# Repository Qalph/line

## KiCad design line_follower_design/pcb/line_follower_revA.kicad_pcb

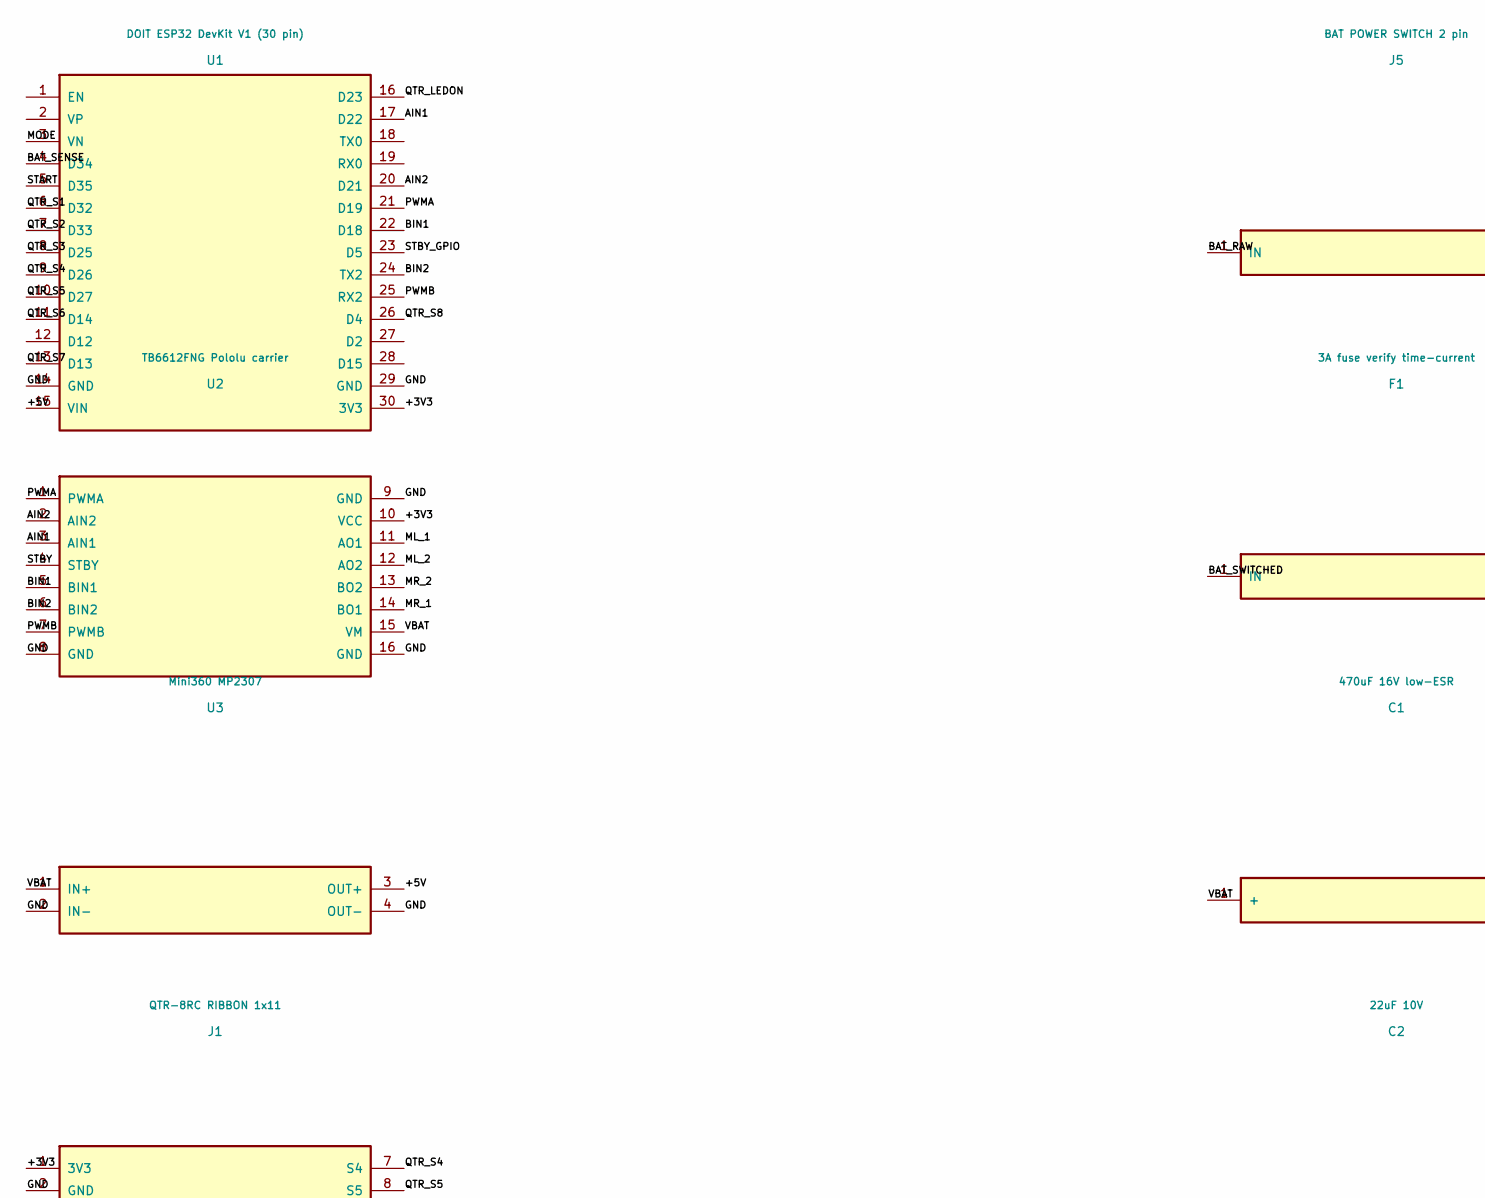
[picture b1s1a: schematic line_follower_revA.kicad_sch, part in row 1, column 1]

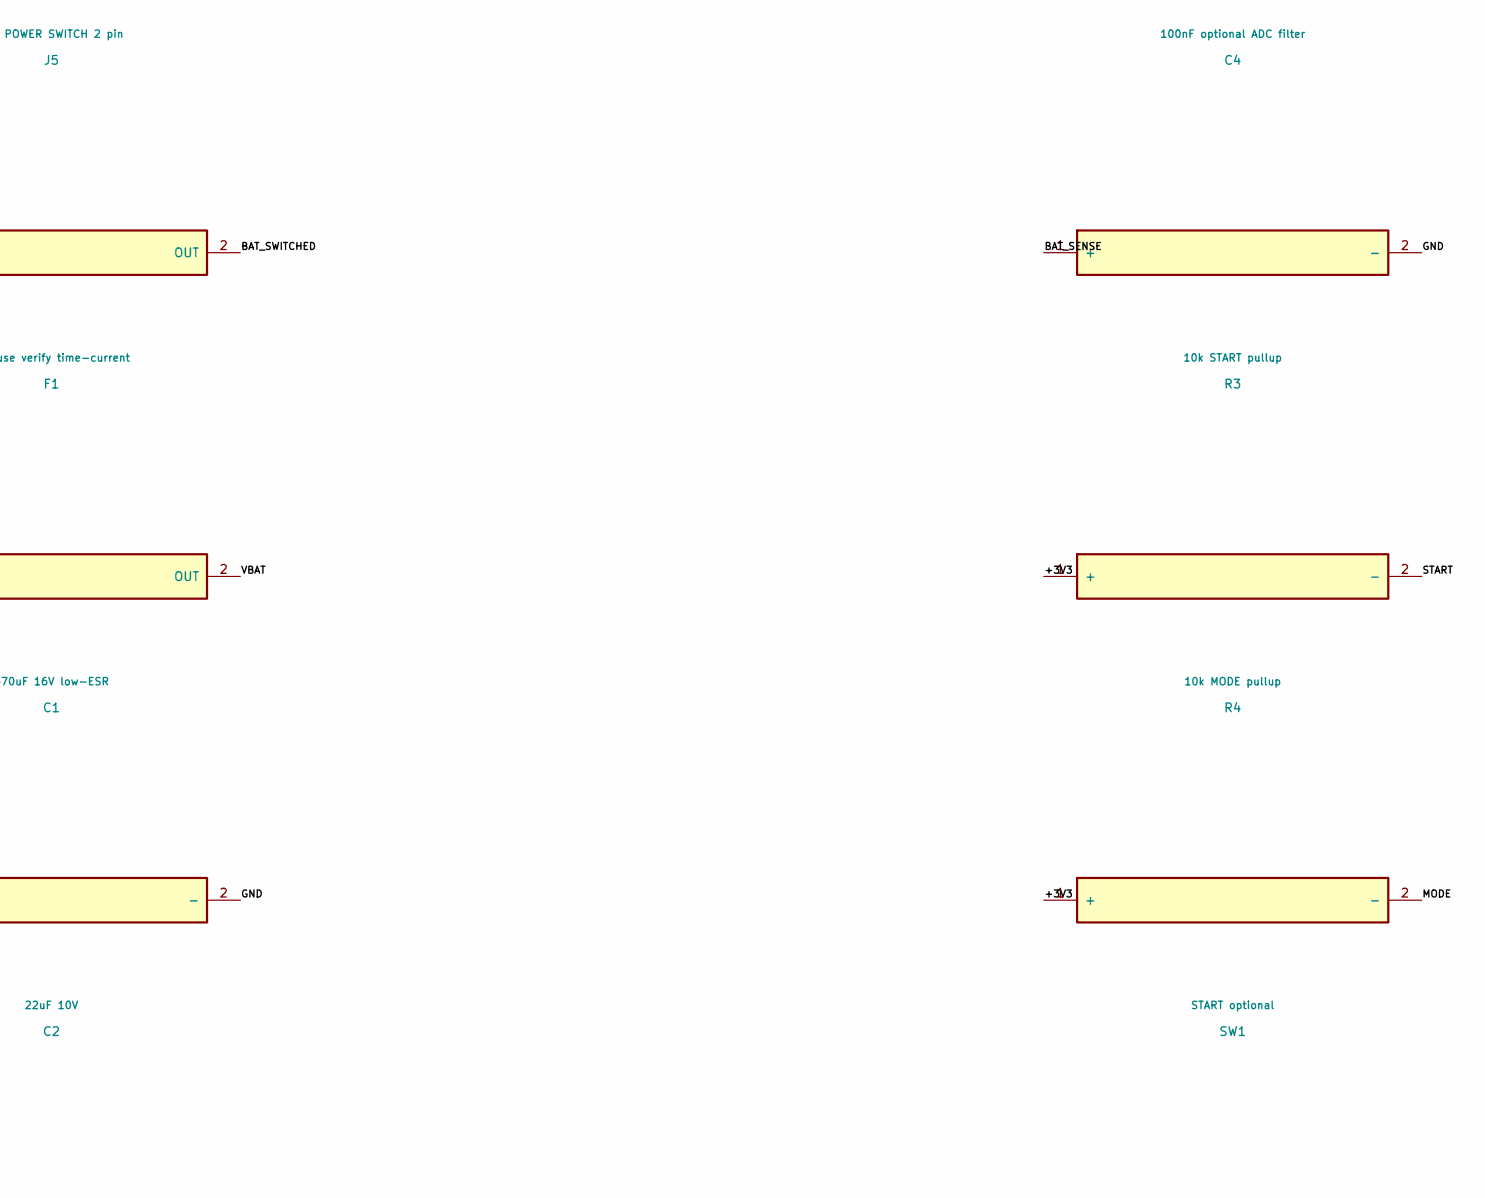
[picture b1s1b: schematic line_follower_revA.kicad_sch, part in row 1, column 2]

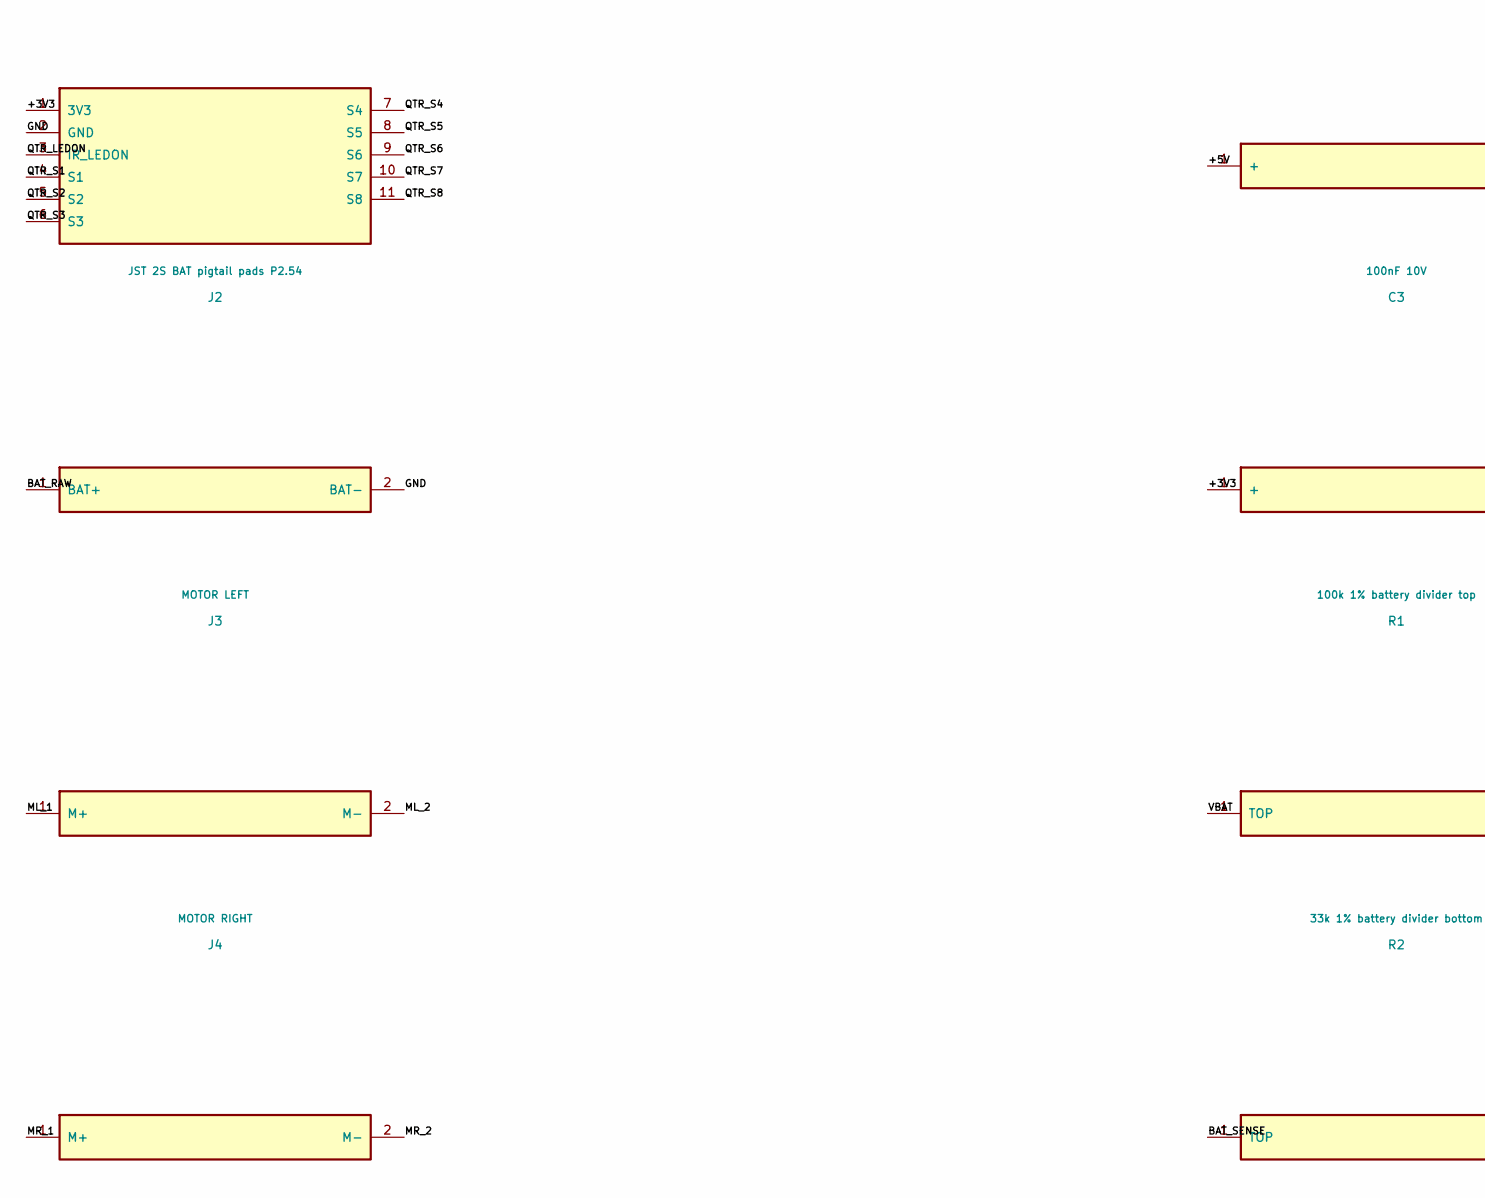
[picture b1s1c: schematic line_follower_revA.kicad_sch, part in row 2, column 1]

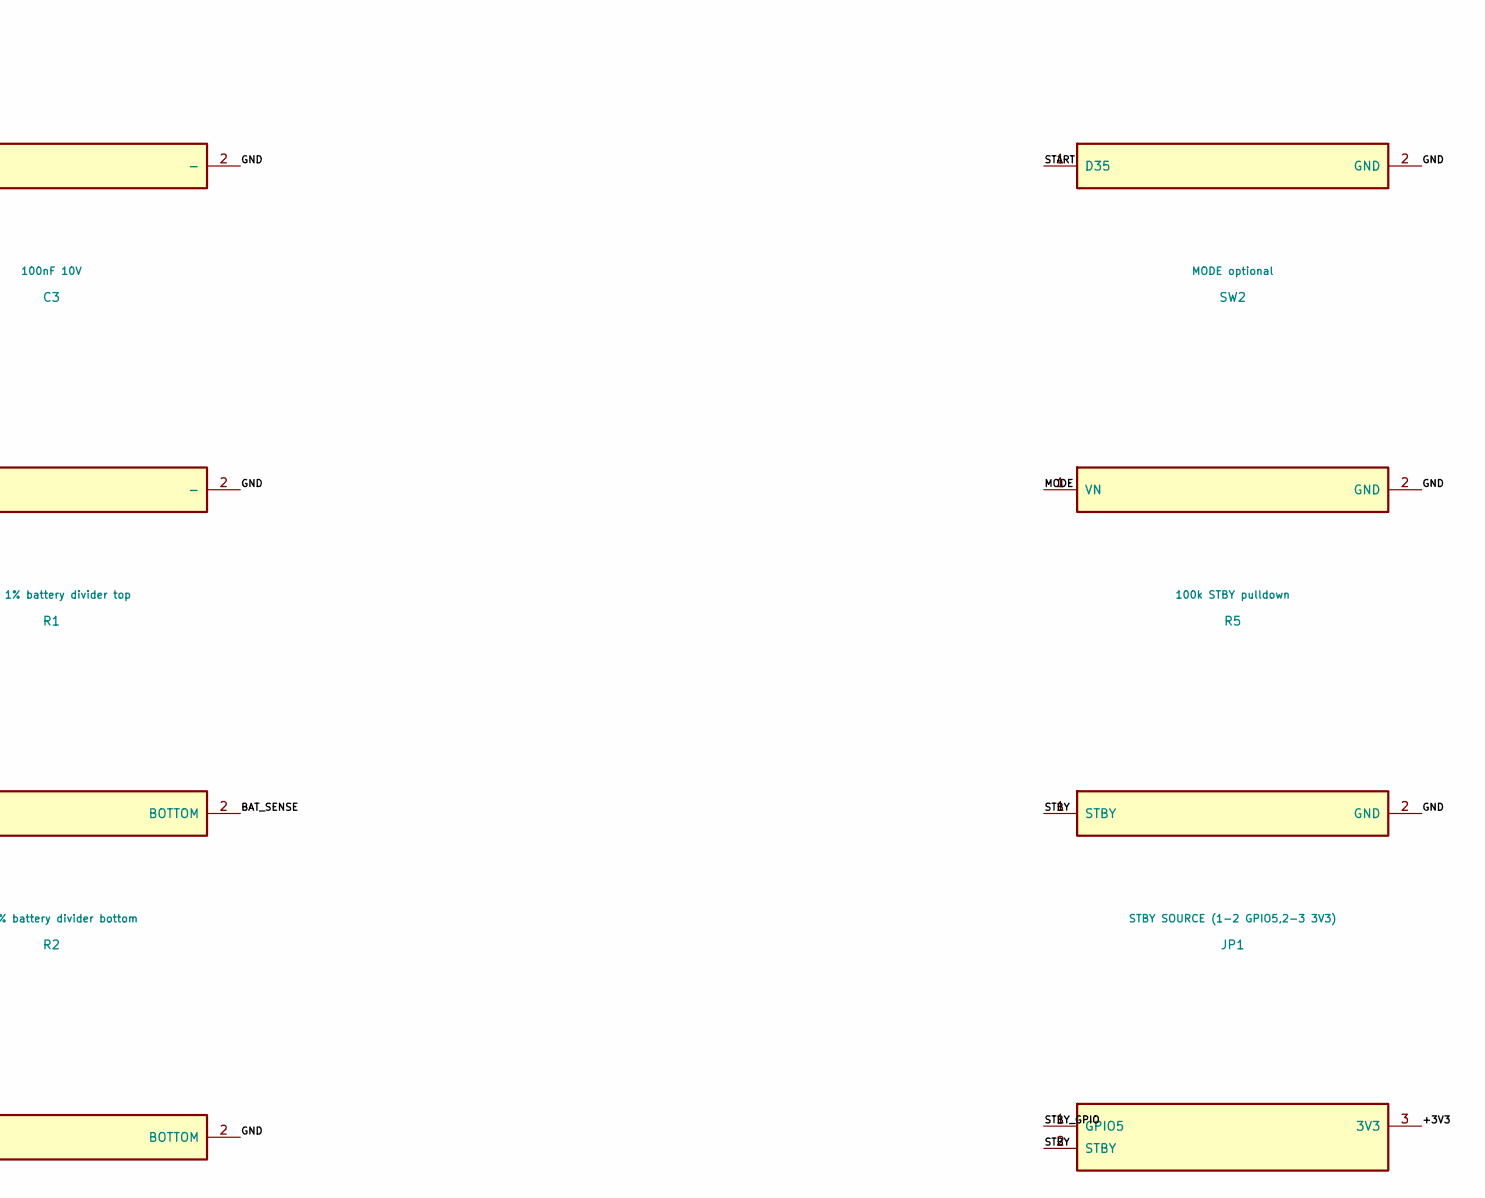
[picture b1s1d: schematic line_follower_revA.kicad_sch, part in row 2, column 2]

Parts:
C1: 470uF 16V low-ESR; CP_Radial_D8_P3.5
C2: 22uF 10V; C_0805
C3: 100nF 10V; C_0603
C4: 100nF optional ADC filter; C_0603
F1: 3A fuse verify time-current; Fuse_1206
J1: QTR-8RC RIBBON 1x11; Conn_1x11
J2: JST 2S BAT pigtail pads P2.54; JST_PIGTAIL_MEASURE
J3: MOTOR LEFT; Conn_1x02
J4: MOTOR RIGHT; Conn_1x02
J5: BAT POWER SWITCH 2 pin; Conn_1x02
JP1: STBY SOURCE (1-2 GPIO5,2-3 3V3); SJ_3
R1: 100k 1% battery divider top; R_0603
R2: 33k 1% battery divider bottom; R_0603
R3: 10k START pullup; R_0603
R4: 10k MODE pullup; R_0603
R5: 100k STBY pulldown; R_0603
SW1: START optional; SW_SMD_MEASURE
SW2: MODE optional; SW_SMD_MEASURE
U1: DOIT ESP32 DevKit V1 (30 pin); ESP32_30
U2: TB6612FNG Pololu carrier; TB6612_Pololu_713
U3: Mini360 MP2307; Mini360_MEASURE

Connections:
+3V3: C3.1 (+), J1.1 (3V3), JP1.3 (3V3), R3.1 (+), R4.1 (+), U1.30 (3V3), U2.10 (VCC)
+5V: C2.1 (+), U1.15 (VIN), U3.3 (OUT+)
AIN1: U1.17 (D22), U2.3 (AIN1)
AIN2: U1.20 (D21), U2.2 (AIN2)
BAT_RAW: J2.1 (BAT+), J5.1 (IN)
BAT_SENSE: C4.1 (+), R1.2 (BOTTOM), R2.1 (TOP), U1.4 (D34)
BAT_SWITCHED: F1.1 (IN), J5.2 (OUT)
BIN1: U1.22 (D18), U2.5 (BIN1)
BIN2: U1.24 (TX2), U2.6 (BIN2)
GND: C1.2 (-), C2.2 (-), C3.2 (-), C4.2 (-), J1.2 (GND), J2.2 (BAT-), R2.2 (BOTTOM), R5.2 (GND), SW1.2 (GND), SW2.2 (GND), U1.14 (GND), U1.29 (GND), U2.8 (GND), U2.9 (GND), U2.16 (GND), U3.2 (IN-), U3.4 (OUT-)
ML_1: J3.1 (M+), U2.11 (AO1)
ML_2: J3.2 (M-), U2.12 (AO2)
MODE: R4.2 (-), SW2.1 (VN), U1.3 (VN)
MR_1: J4.1 (M+), U2.14 (BO1)
MR_2: J4.2 (M-), U2.13 (BO2)
PWMA: U1.21 (D19), U2.1 (PWMA)
PWMB: U1.25 (RX2), U2.7 (PWMB)
QTR_LEDON: J1.3 (IR_LEDON), U1.16 (D23)
QTR_S1: J1.4 (S1), U1.6 (D32)
QTR_S2: J1.5 (S2), U1.7 (D33)
QTR_S3: J1.6 (S3), U1.8 (D25)
QTR_S4: J1.7 (S4), U1.9 (D26)
QTR_S5: J1.8 (S5), U1.10 (D27)
QTR_S6: J1.9 (S6), U1.11 (D14)
QTR_S7: J1.10 (S7), U1.13 (D13)
QTR_S8: J1.11 (S8), U1.26 (D4)
START: R3.2 (-), SW1.1 (D35), U1.5 (D35)
STBY: JP1.2 (STBY), R5.1 (STBY), U2.4 (STBY)
STBY_GPIO: JP1.1 (GPIO5), U1.23 (D5)
VBAT: C1.1 (+), F1.2 (OUT), R1.1 (TOP), U2.15 (VM), U3.1 (IN+)

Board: 2 copper layers, 25 parts (0 on the bottom side), 30 nets, no tracks yet.

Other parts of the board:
H_74_71, H_74_128, H_126_71, H_126_128: M3; MountingHole_M3

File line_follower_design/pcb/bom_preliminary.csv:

Ref,Value,Footprint,Quantity,Status / measurement required
C1,470uF 16V low-ESR,LF:CP_Radial_D8_P3.5,1,Polarity + to VBAT; at TB6612 VM
C2,22uF 10V,LF:C_0805,1,Choose low-ESR X7R or appropriate 10V rating
C3,100nF 10V,LF:C_0603,1,3V3 decoupling; route close to output/ESP
C4,100nF optional ADC filter,LF:C_0603,1,Optional/DNP; filter with source impedance
F1,3A fuse verify time-current,LF:Fuse_1206,1,"3A 1206 fuse selection not final; measure stall/inrush, choose voltage interrupt rating"
J1,QTR-8RC RIBBON 1x11,LF:Conn_1x11,1,Order is controller header only; QTR sensor module orientation to be verified; S1 at robot left
J2,JST 2S BAT pigtail pads P2.54,LF:JST_PIGTAIL_MEASURE,1,NOT a verified JST mating connector; 2.54 PTH pads for JST pigtail pending choice of actual connector
J3,MOTOR LEFT,LF:Conn_1x02,1,Motor leads require adequate strain relief
J4,MOTOR RIGHT,LF:Conn_1x02,1,Right motor connector offset inward due to rear power crowding
J5,BAT POWER SWITCH 2 pin,LF:Conn_1x02,1,External in-line switch 2-pad footprint: replace with matching on-board switch after measuring
JP1,"STBY SOURCE (1-2 GPIO5,2-3 3V3)",LF:SJ_3,1,Default bridge 1-2; only use 2-3 when safe to energize on boot
R1,100k 1% battery divider top,LF:R_0603,1,ADC1_GPIO34
R2,33k 1% battery divider bottom,LF:R_0603,1,ADC calibrate against multimeter
R3,10k START pullup,LF:R_0603,1,Required input-only D35 external pull-up
R4,10k MODE pullup,LF:R_0603,1,Required input-only VN/GPIO39 external pull-up
R5,100k STBY pulldown,LF:R_0603,1,Keeps motors in standby at ESP32 reset
SW1,START optional,LF:SW_SMD_MEASURE,1,Optional side-edge SMD switch: choose real footprint
SW2,MODE optional,LF:SW_SMD_MEASURE,1,Optional side-edge SMD switch: choose real footprint
U1,DOIT ESP32 DevKit V1 (30 pin),LF:ESP32_30,1,PIN 1 LOCATION AND ROW GAP 25.4 MUST BE MEASURED; USB to +X
U2,TB6612FNG Pololu carrier,LF:TB6612_Pololu_713,1,"Pololu #713 footprint: rows 12.70mm, 8 pins 2.54mm apart; verify pin 1"
U3,Mini360 MP2307,LF:Mini360_MEASURE,1,Four holes are NONSTANDARD across Mini-360 clones - measurement required

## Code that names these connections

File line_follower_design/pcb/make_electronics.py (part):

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emap={
 'D34':'BAT_SENSE','D35':'START','D32':'QTR_S1','D33':'QTR_S2','D25':'QTR_S3','D26':'QTR_S4',
 'D27':'QTR_S5','D14':'QTR_S6','D13':'QTR_S7','VIN':'+5V','D23':'QTR_LEDON',
 'D22':'AIN1','D21':'AIN2','D19':'PWMA','D18':'BIN1','D5':'STBY_GPIO',
 'TX2':'BIN2','RX2':'PWMB','D4':'QTR_S8','3V3':'+3V3','GND':'GND',
 'VN':'MODE',
}
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comp('J2','JST 2S BAT pigtail pads P2.54','LF:JST_PIGTAIL_MEASURE','LF:JST_PIGTAIL_MEASURE',(23,-10),[(1,'BAT+','BAT_RAW'),(2,'BAT-','GND')],(5,8),'NOT a verified JST mating connector; 2.54 PTH pads for JST pigtail pending choice of actual connector')
comp('J3','MOTOR LEFT','LF:Conn_1x02','LF:Conn_1x02',(-19,-27.5),[(1,'M+','ML_1'),(2,'M-','ML_2')],(5,6),'Motor leads require adequate strain relief')
comp('J4','MOTOR RIGHT','LF:Conn_1x02','LF:Conn_1x02',(14,-18),[(1,'M+','MR_1'),(2,'M-','MR_2')],(5,6),'Right motor connector offset inward due to rear power crowding')
comp('J5','BAT POWER SWITCH 2 pin','LF:Conn_1x02','LF:Conn_1x02',(26,-18),[(1,'IN','BAT_RAW'),(2,'OUT','BAT_SWITCHED')],(5,6),'External in-line switch 2-pad footprint: replace with matching on-board switch after measuring')
comp('F1','3A fuse verify time-current','LF:Fuse_1206','LF:Fuse_1206',(24,-25),[(1,'IN','BAT_SWITCHED'),(2,'OUT','VBAT')],(3.6,2.0),'3A 1206 fuse selection not final; measure stall/inrush, choose voltage interrupt rating')
comp('C1','470uF 16V low-ESR','LF:CP_Radial_D8_P3.5','LF:CP_Radial_D8_P3.5',(17,-26),[(1,'+','VBAT'),(2,'-','GND')],(8,8),'Polarity + to VBAT; at TB6612 VM')
comp('C2','22uF 10V','LF:C_0805','LF:C_0805',(-20,-7.5),[(1,'+','+5V'),(2,'-','GND')],(2.0,1.25),'Choose low-ESR X7R or appropriate 10V rating')
comp('C3','100nF 10V','LF:C_0603','LF:C_0603',(-15,-7.5),[(1,'+','+3V3'),(2,'-','GND')],(1.6,.8),'3V3 decoupling; route close to output/ESP')
comp('R1','100k 1% battery divider top','LF:R_0603','LF:R_0603',(7,-10),[(1,'TOP','VBAT'),(2,'BOTTOM','BAT_SENSE')],(1.6,.8),'ADC1_GPIO34')
comp('R2','33k 1% battery divider bottom','LF:R_0603','LF:R_0603',(11,-10),[(1,'TOP','BAT_SENSE'),(2,'BOTTOM','GND')],(1.6,.8),'ADC calibrate against multimeter')
comp('C4','100nF optional ADC filter','LF:C_0603','LF:C_0603',(15,-10),[(1,'+','BAT_SENSE'),(2,'-','GND')],(1.6,.8),'Optional/DNP; filter with source impedance')
comp('R3','10k START pullup','LF:R_0603','LF:R_0603',(-27,3),[(1,'+','+3V3'),(2,'-','START')],(1.6,.8),'Required input-only D35 external pull-up')
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comp('SW1','START optional','LF:SW_SMD_MEASURE','LF:SW_SMD_MEASURE',(-28.3,7),[(1,'D35','START'),(2,'GND','GND')],(3,3.2),'Optional side-edge SMD switch: choose real footprint')
comp('SW2','MODE optional','LF:SW_SMD_MEASURE','LF:SW_SMD_MEASURE',(-28.3,19),[(1,'VN','MODE'),(2,'GND','GND')],(3,3.2),'Optional side-edge SMD switch: choose real footprint')
comp('R5','100k STBY pulldown','LF:R_0603','LF:R_0603',(4,-10),[(1,'STBY','STBY'),(2,'GND','GND')],(1.6,.8),'Keeps motors in standby at ESP32 reset')
comp('JP1','STBY SOURCE (1-2 GPIO5,2-3 3V3)','LF:SJ_3','LF:SJ_3',(0,-10),[(1,'GPIO5','STBY_GPIO'),(2,'STBY','STBY'),(3,'3V3','+3V3')],(3.2,1.6),'Default bridge 1-2; only use 2-3 when safe to energize on boot')
# Pin index netlist exported below.
NETS=collections.defaultdict(list)
for ref,pl in PINS.items():
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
